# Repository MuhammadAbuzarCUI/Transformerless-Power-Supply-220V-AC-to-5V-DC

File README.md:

# PCB card Transformerless-Power-Supply-220V-AC-to-5V-DC
A transformerless power supply is an electronic circuit designed to convert 220V AC mains voltage into a low-voltage DC output of 5V without using a bulky transformer. It typically uses a capacitive voltage-dropping circuit, rectifier diodes, a filter capacitor, and a 5V voltage regulator to provide a DC supply for low-power electronic circuits.

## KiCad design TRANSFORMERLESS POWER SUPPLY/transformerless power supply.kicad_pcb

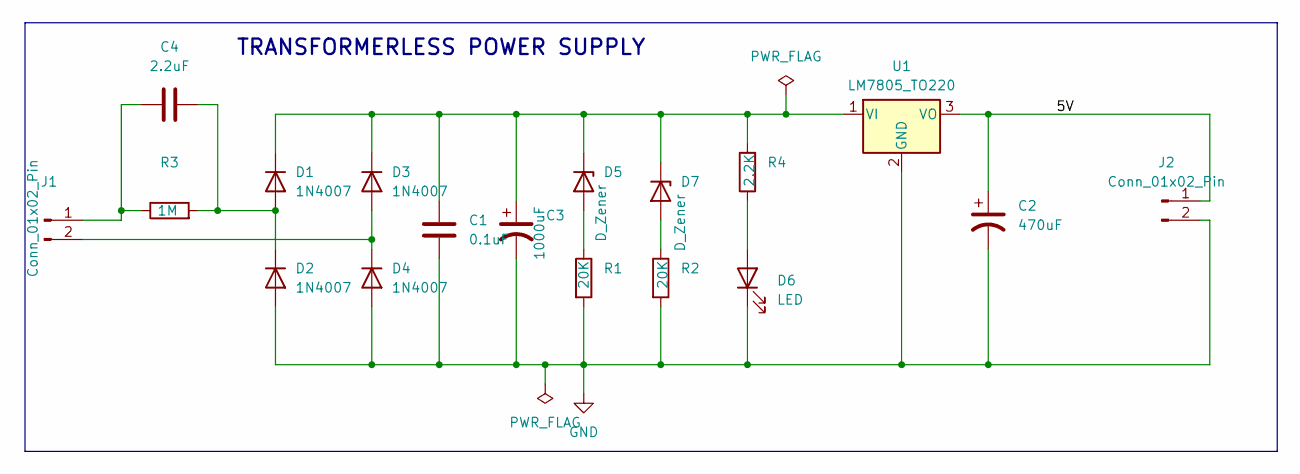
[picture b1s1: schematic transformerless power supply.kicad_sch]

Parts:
C1: 0.1uF; C_Disc_D4.7mm_W2.5mm_P5.00mm
C2: 470uF; CP_Radial_D10.0mm_P5.00mm
C3: 1000uF; CP_Radial_D10.0mm_P3.80mm
C4: 2.2uF; C_Rect_L18.0mm_W5.0mm_P15.00mm_FKS3_FKP3
D1, D2, D3, D4: 1N4007; D_DO-35_SOD27_P10.16mm_Horizontal
D5, D7: D_Zener; D_A-405_P7.62mm_Horizontal
D6: LED; LED_D5.0mm
J1, J2: Conn_01x02_Pin; PinHeader_1x02_P2.54mm_Horizontal
R1, R2: 20K; R_Axial_DIN0207_L6.3mm_D2.5mm_P7.62mm_Horizontal
R3: 1M; R_Axial_DIN0207_L6.3mm_D2.5mm_P7.62mm_Horizontal
R4: 2.2K; R_Axial_DIN0207_L6.3mm_D2.5mm_P7.62mm_Horizontal
U1: LM7805_TO220; TO-220-3_Vertical

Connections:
/5V: C2.1, J2.1, U1.3 (VO)
GND: C1.2, C2.2, C3.2, D2.2 (A), D4.2 (A), D6.1 (K), J2.2, R1.2, R2.2, U1.2 (GND)
unnamed: C4.2, D1.2 (A), D2.1 (K), R3.2
unnamed: C1.1, C3.1, D1.1 (K), D3.1 (K), D5.1 (K), D7.1 (K), R4.2, U1.1 (VI)
unnamed: D3.2 (A), D4.1 (K), J1.2
unnamed: D5.2 (A), R1.1
unnamed: D6.2 (A), R4.1
unnamed: D7.2 (A), R2.1
unnamed: C4.1, J1.1, R3.1

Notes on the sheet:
TRANSFORMERLESS POWER SUPPLY

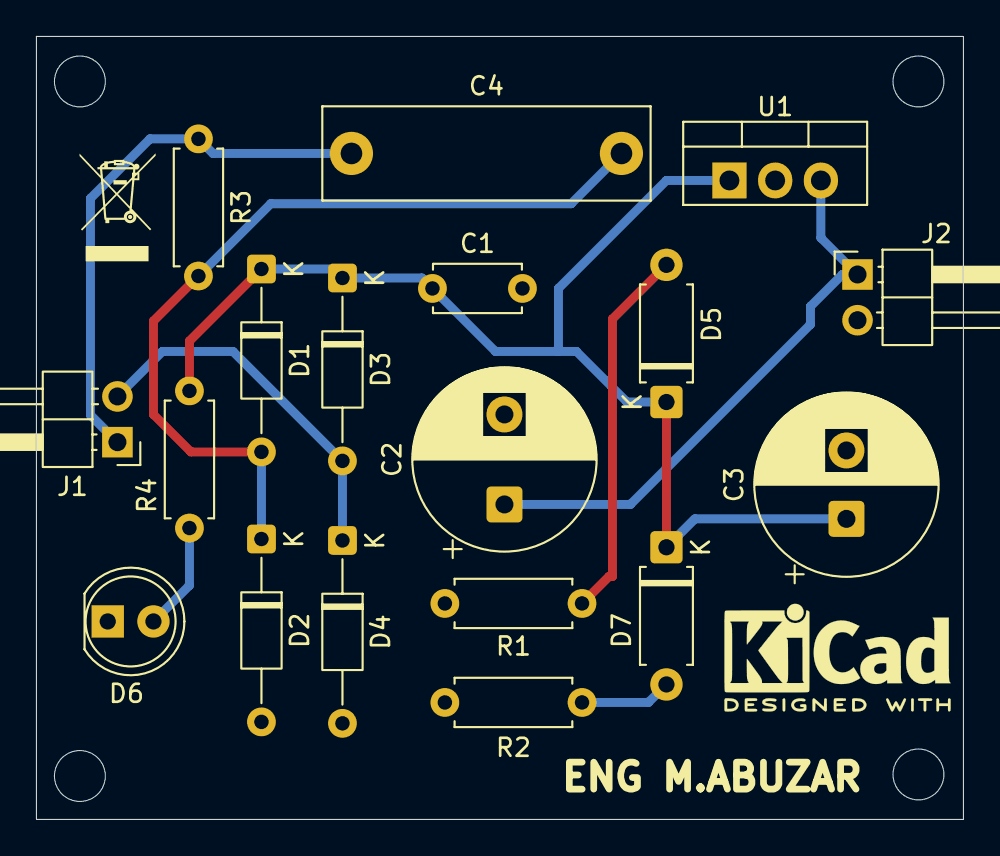
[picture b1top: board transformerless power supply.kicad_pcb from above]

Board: 2 copper layers, 51.5 x 43.5 mm, 18 parts (0 on the bottom side), 9 nets.
